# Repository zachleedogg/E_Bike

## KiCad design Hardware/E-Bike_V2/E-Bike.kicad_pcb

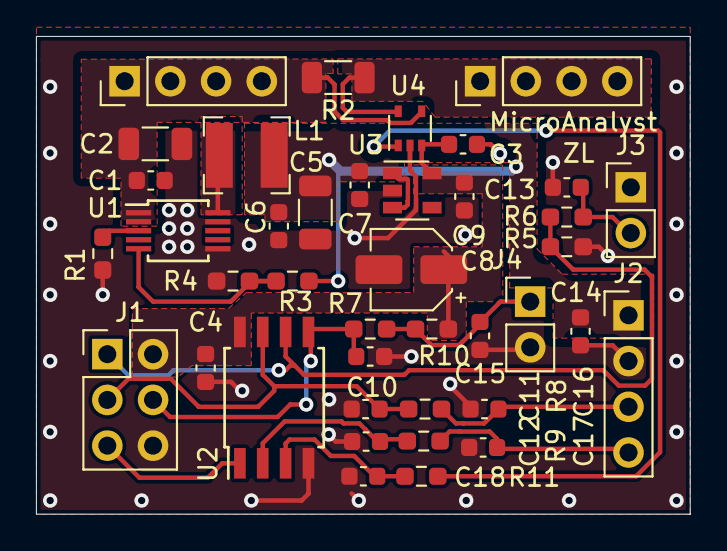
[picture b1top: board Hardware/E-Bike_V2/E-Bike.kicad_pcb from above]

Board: 2 copper layers, 36.3 x 26.5 mm, 40 parts (0 on the bottom side), 19 nets.

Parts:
C1, C10, C11, C12, C15, C16, C17, C18: 10n; C_0603_1608Metric
C2: 1u; C_1206_3216Metric
C3, C4, C6, C9: 100n; C_0603_1608Metric
C5: 10u; C_1206_3216Metric
C7, C13, C14: 1u; C_0603_1608Metric
C8: 4u7; CP_Elec_4x5.4
J1: AVR-ISP-6; PinHeader_2x03_P2.54mm_Vertical
J2, J5, J6: Conn_01x04; PinHeader_1x04_P2.54mm_Vertical
J3, J4: Conn_01x02; PinHeader_1x02_P2.54mm_Vertical
L1: 150u; L_Bourns-SRN4018
R1: 69.8k; R_0603_1608Metric_Pad0.98x0.95mm_HandSolder
R2: R0005; R_1206_3216Metric
R3: 576k; R_0603_1608Metric_Pad0.98x0.95mm_HandSolder
R4: 49k9; R_0603_1608Metric_Pad0.98x0.95mm_HandSolder
R5, R6, R7, R8, R9, R10, R11: 10k; R_0603_1608Metric_Pad0.98x0.95mm_HandSolder
U1: MAX17552AUB+; MSOP-10_3x3mm_P0.5mm
U2: ATtiny85-20SU; SOIJ-8_5.3x5.3mm_P1.27mm
U3: TPS76350; SOT-23-5
U4: INA290; SOT-353_SC-70-5

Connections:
+5V: C3.1, C4.1, C8.1, C9.1, J1.2, R10.1, U2.8, U3.5, U4.3
+10V: C5.1, C6.1, C7.1, C14.1, J2.1, L1.2, R3.1, U3.1, U3.3
/VBUS_R: J6.1, J6.2, J6.3, J6.4, R2.1, U4.5
BUTTON_IN: C15.1, J4.1, R7.2, R10.2
CADENCE_IN: C16.1, J2.3, R8.2
GND: C1.2, C2.2, C3.2, C4.2, C5.2, C6.2, C7.2, C8.2, C9.2, C10.2, C11.2, C12.2, C13.2, C14.2, C15.2, C16.2, C17.2, C18.2, J1.6, J2.2, J3.1, J4.2, R1.2, R4.2, R5.2, U1.6, U1.9, U2.4, U3.2, U4.2
unnamed: C10.1, J1.4, R7.1, U2.5
unnamed: C11.1, J1.3, R8.1, U2.7
unnamed: C12.1, R9.1, U2.2
unnamed: C18.1, R11.2, U2.3
unnamed: J1.1, R5.1, R6.1, U2.6
unnamed: J1.5, U2.1
unnamed: L1.1, U1.10
unnamed: R1.1, U1.3
unnamed: R3.2, R4.1, U1.5
unnamed: R11.1, U4.1
PWM_OUT: C13.1, J3.2, R6.2
TORQUE_IN: C17.1, J2.4, R9.2
VBUS: C1.1, C2.1, J5.1, J5.2, J5.3, J5.4, R2.2, U1.1, U1.2, U4.4

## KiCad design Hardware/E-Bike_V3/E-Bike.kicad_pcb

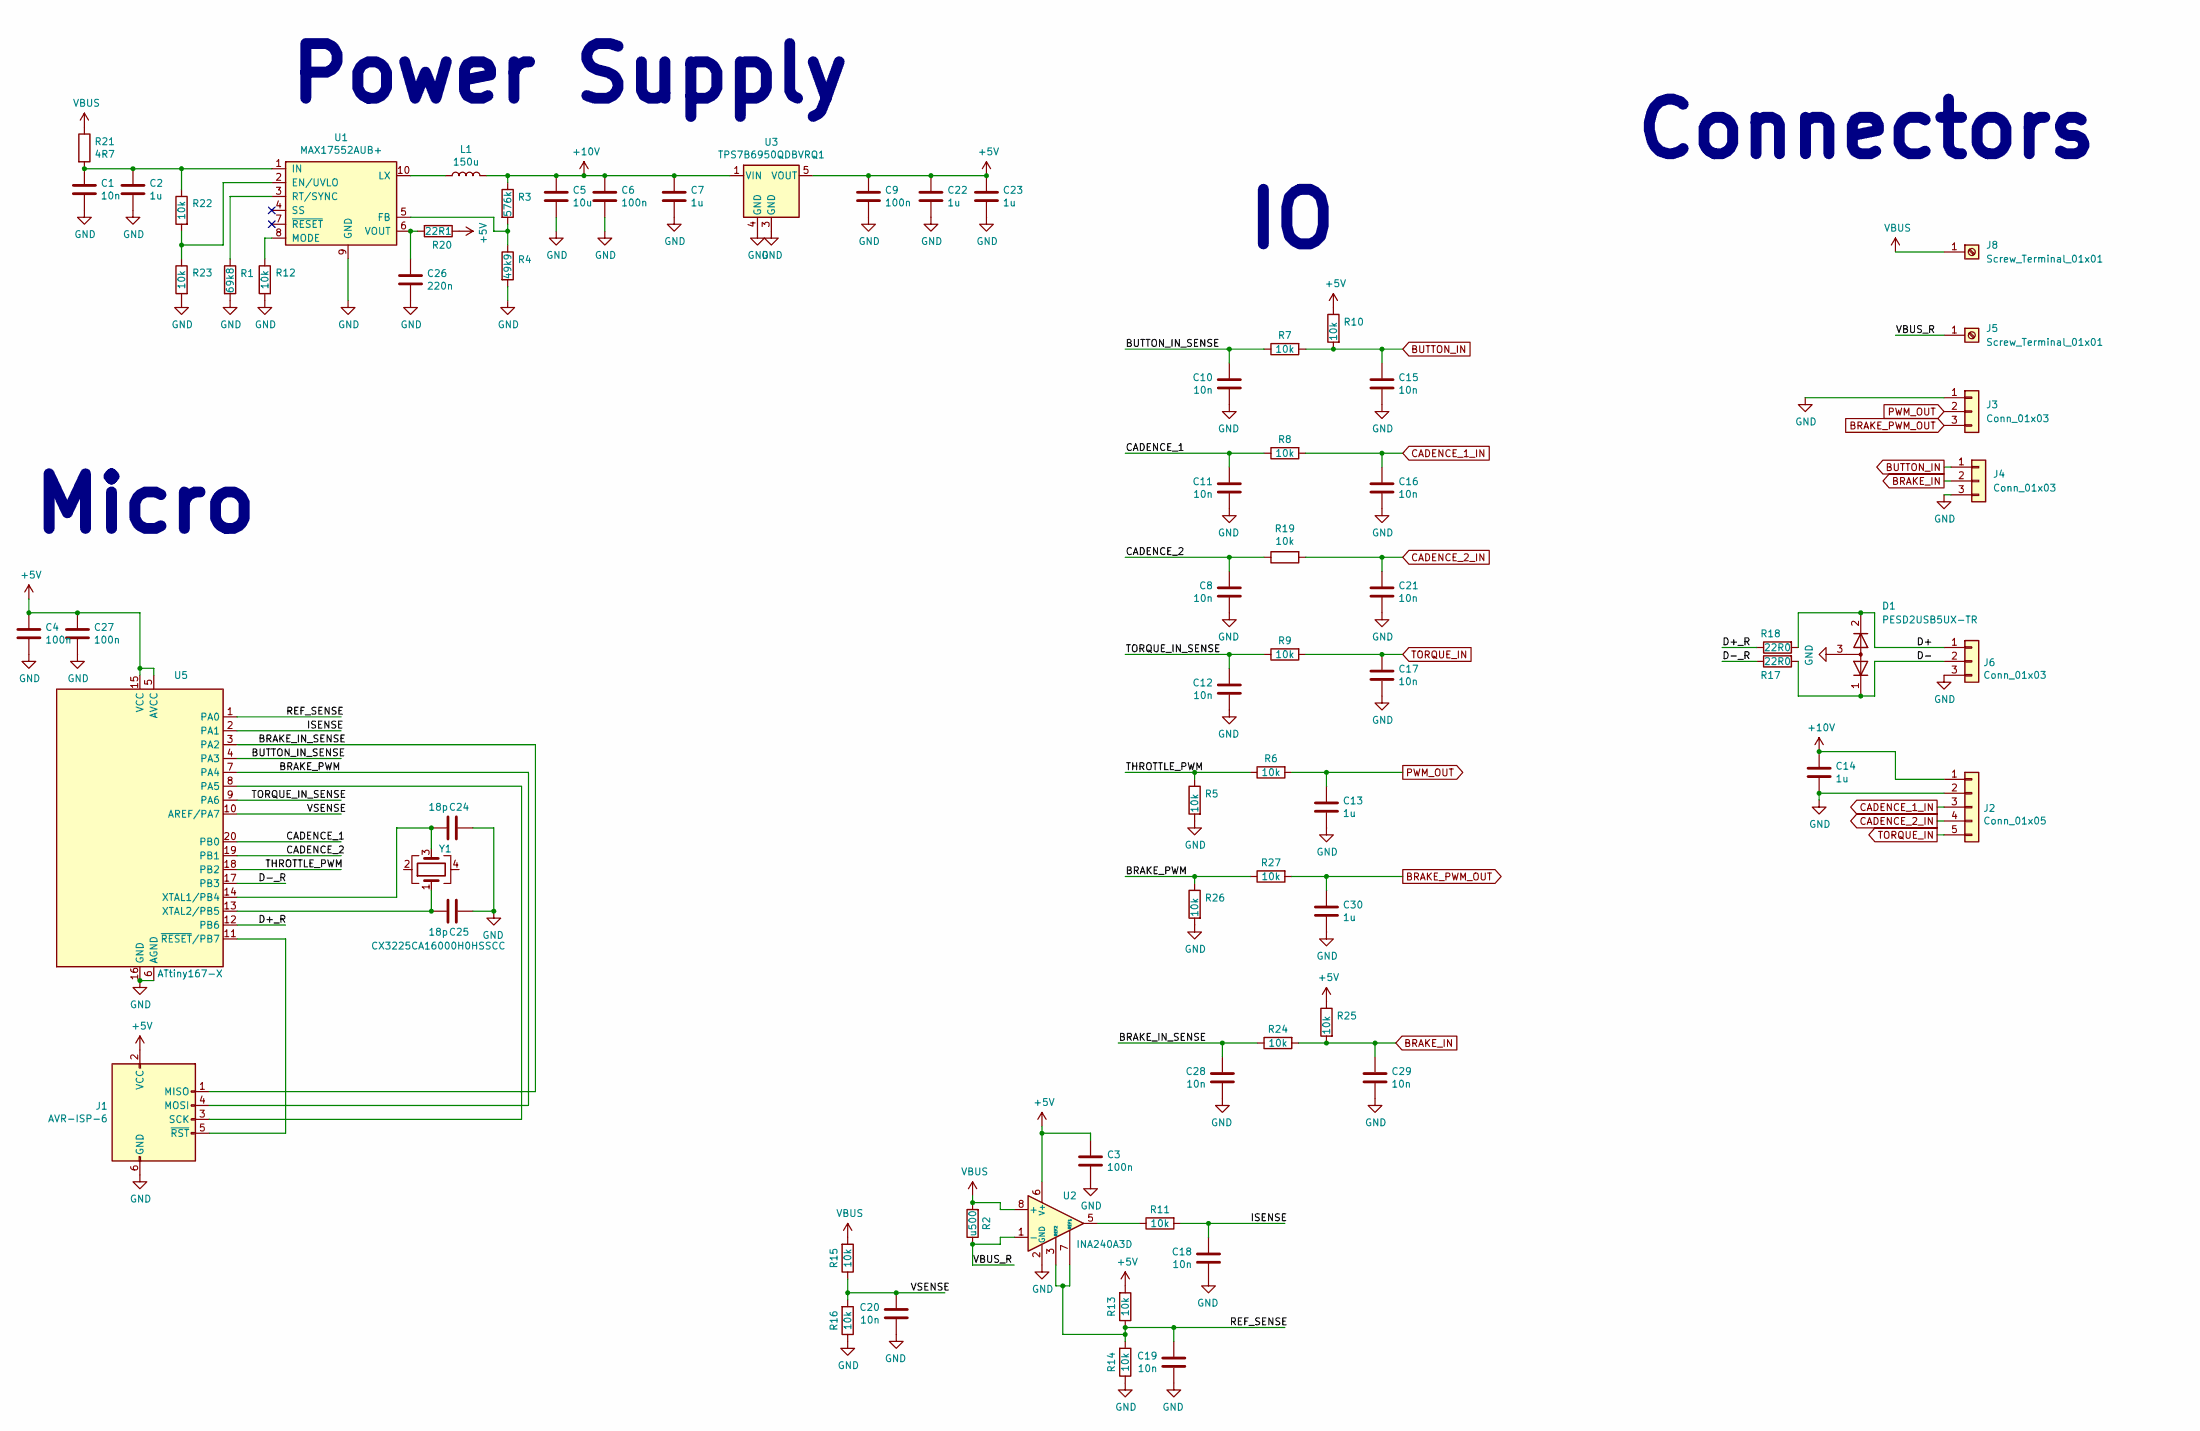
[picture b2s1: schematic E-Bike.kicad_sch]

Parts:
C1, C8, C10, C11, C12, C15, C16, C17, C18, C19, C20, C21, C28, C29: 10n; C_0603_1608Metric; Part Number 06035C103JAT2A
C2: 1u; C_1206_3216Metric; Part Number C3216X7R2A105K160AA
C3, C4, C6, C9, C27: 100n; C_0603_1608Metric; Part Number CL10B104KB8WPND
C5: 10u; C_1206_3216Metric; Part Number CGA5L1X7R1E106K160AE
C7, C13, C14, C22, C23, C30: 1u; C_0603_1608Metric; Part Number CL21B105KOFVPNE
C24, C25: 18p; C_0603_1608Metric
C26: 220n; C_0603_1608Metric
D1: PESD2USB5UX-TR; TSOT-23
J1: AVR-ISP-6; PinHeader_2x03_P2.54mm_Vertical
J2: Conn_01x05; PinHeader_1x05_P2.54mm_Vertical
J3, J4, J6: Conn_01x03; PinHeader_1x03_P2.54mm_Vertical
J5, J8: Screw_Terminal_01x01; MountingHole_4.3mm_M4_DIN965_Pad
L1: 150u; L_Bourns-SRN4018; Part Number SRN4026-151M
R1: 69k8; C_0603_1608Metric; Part Number RMCF0603FT69K8
R2: u500; R_1206_3216Metric; Part Number HCS1206FTL500
R3: 576k; C_0603_1608Metric; Part Number RNCF0603DTC576K
R4: 49k9; C_0603_1608Metric; Part Number ERJ-3EKF4992V
R5, R6, R7, R8, R9, R10, R11, R12, R13, R14, R15, R16, R19, R22, R23, R24, R25, R26, R27: 10k; C_0603_1608Metric; Part Number CRGCQ0603F10K
R17, R18: 22R0; C_0603_1608Metric
R20: 22R1; C_0603_1608Metric
R21: 4R7; C_0603_1608Metric
U1: MAX17552AUB+; MSOP-10_3x3mm_P0.5mm; Part Number MAX17552AUB+
U2: INA240A3D; SOIC-8_3.9x4.9mm_P1.27mm
U3: TPS7B6950QDBVRQ1; SOT-23-5; Part Number TPS7B6950QDBVRQ1
U5: ATtiny167-X; TSSOP-20_4.4x6.5mm_P0.65mm
Y1: CX3225CA16000H0HSSCC; Crystal_SMD_3225-4Pin_3.2x2.5mm

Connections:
+5V: C3.1, C4.1, C9.1, C22.1, C23.1, C27.1, J1.2 (VCC), R10.1, R13.2, R20.1, R25.1, U2.6 (V+), U3.5 (VOUT), U5.5 (AVCC), U5.15 (VCC)
+10V: C5.1, C6.1, C7.1, C14.1, J2.1, L1.2, R3.1, U3.1 (VIN)
/BRAKE_IN_SENSE: C28.1, J1.1 (MISO), R24.1, U5.3 (PA2)
/BRAKE_PWM: J1.4 (MOSI), R26.1, R27.1, U5.7 (PA4)
/BUTTON_IN_SENSE: C10.1, R7.1, U5.4 (PA3)
/CADENCE_1: C11.1, R8.1, U5.20 (PB0)
/CADENCE_2: C8.1, R19.1, U5.19 (PB1)
/D+: D1.2 (K), J6.1, R18.2
/D+_R: R18.1, U5.12 (PB6)
/D-: D1.1 (K), J6.2, R17.2
/D-_R: R17.1, U5.17 (PB3)
/ISENSE: C18.1, R11.2, U5.2 (PA1)
/REF_SENSE: C19.1, R13.1, R14.2, U2.3 (REF2), U2.7 (REF1), U5.1 (PA0)
/THROTTLE_PWM: R5.1, R6.1, U5.18 (PB2)
/TORQUE_IN_SENSE: C12.1, R9.1, U5.9 (PA6)
/VBUS_R: J5.1, R2.1, U2.1 (-)
/VSENSE: C20.1, R15.1, R16.2, U5.10 (AREF/PA7)
BRAKE_IN: C29.1, J4.2, R24.2, R25.2
BRAKE_PWM_OUT: C30.1, J3.3, R27.2
BUTTON_IN: C15.1, J4.1, R7.2, R10.2
CADENCE_1_IN: C16.1, J2.3, R8.2
CADENCE_2_IN: C21.1, J2.4, R19.2
GND: C1.2, C2.2, C3.2, C4.2, C5.2, C6.2, C7.2, C8.2, C9.2, C10.2, C11.2, C12.2, C13.2, C14.2, C15.2, C16.2, C17.2, C18.2, C19.2, C20.2, C21.2, C22.2, C23.2, C24.2, C25.2, C26.2, C27.2, C28.2, C29.2, C30.2, D1.3 (A), J1.6 (GND), J2.2, J3.1, J4.3, J6.3, R1.2, R4.2, R5.2, R12.2, R14.1, R16.1, R23.2, R26.2, U1.9 (GND), U2.2 (GND), U2.4 (GND), U3.3 (GND), U3.4 (GND), U5.6 (AGND), U5.16 (GND)
unnamed: J1.3 (SCK), U5.8 (PA5)
unnamed: J1.5 (~RST), U5.11 (~RESET/PB7)
unnamed: R11.1, U2.5
unnamed: R22.2, R23.1, U1.2 (EN/UVLO)
unnamed: R3.2, R4.1, U1.5 (FB)
unnamed: C1.1, C2.1, R21.2, R22.1, U1.1 (IN)
unnamed: L1.1, U1.10 (LX)
unnamed: R12.1, U1.8 (MODE)
unnamed: R1.1, U1.3 (RT/SYNC)
unnamed: C26.1, R20.2, U1.6 (VOUT)
unnamed: C24.1, U5.14 (XTAL1/PB4), Y1.3
unnamed: C25.1, U5.13 (XTAL2/PB5), Y1.1
PWM_OUT: C13.1, J3.2, R6.2
TORQUE_IN: C17.1, J2.5, R9.2
VBUS: J8.1, R2.2, R15.2, R21.1, U2.8 (+)

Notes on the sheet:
Micro
Power Supply
Connectors

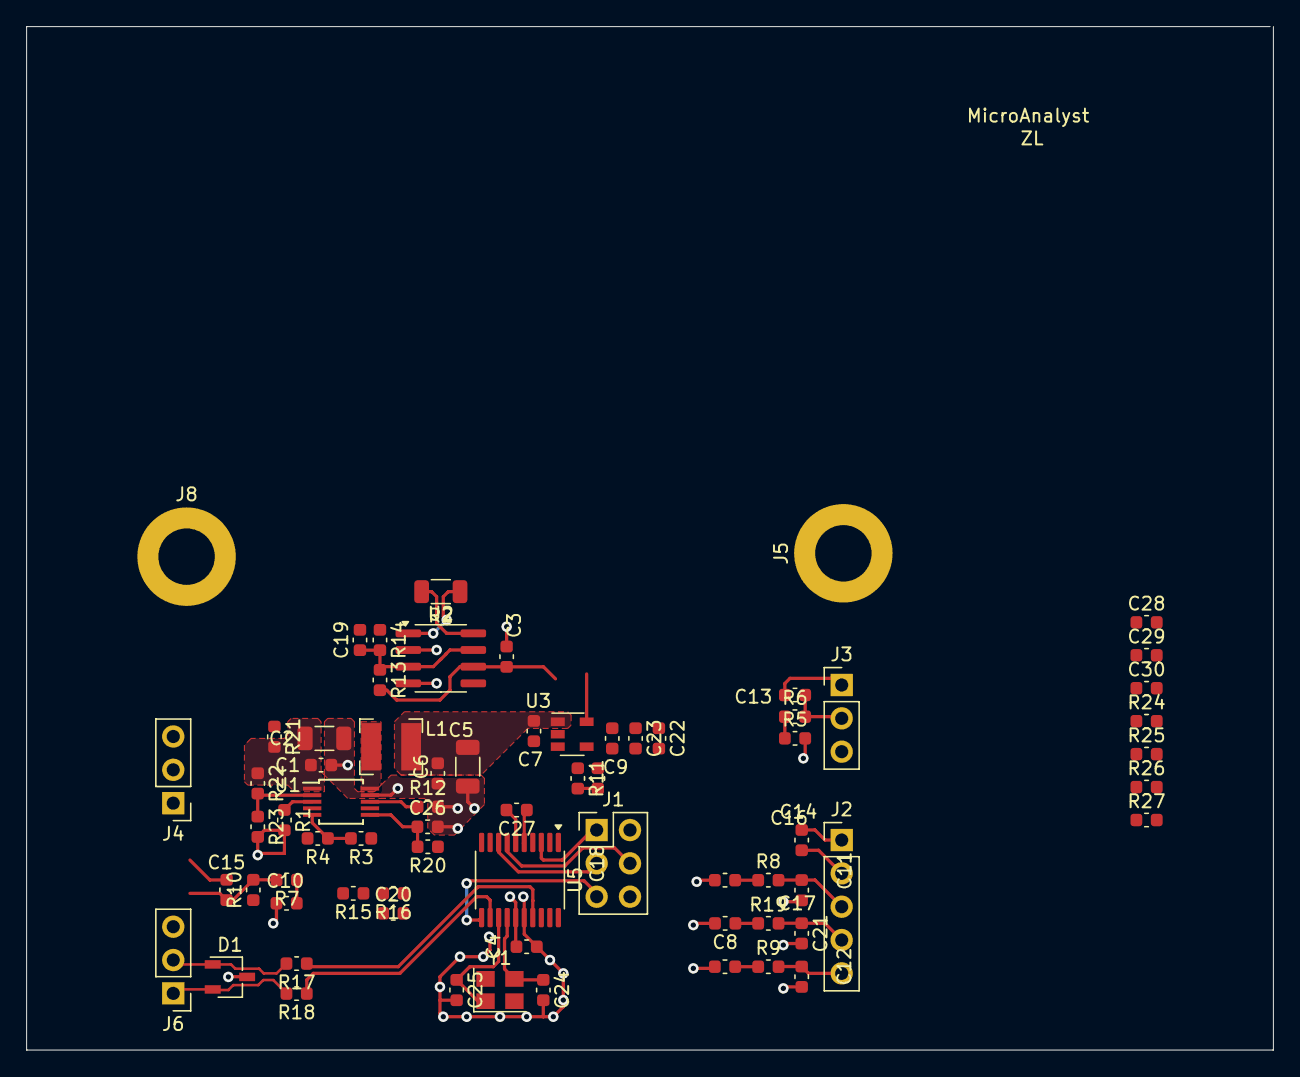
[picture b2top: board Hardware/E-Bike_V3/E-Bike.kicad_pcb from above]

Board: 2 copper layers, 95.0 x 78.0 mm, 71 parts (0 on the bottom side), 38 nets.

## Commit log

2022-02-19 v2 hardware and added arduino PID with current sense sketch
2025-06-29 updated algo for v2, started v3 design
